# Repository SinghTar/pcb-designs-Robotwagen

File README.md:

# PCB designs

## Linetrackerboard versie 1

Hieronder vindt u de schema en de pcb design van de linetrackerbordje.

### schema 

### pcb

### 3D design

## Motorsturing versie 1

Hieronder vindt u de schema en de pcb design van de motorsturing.

### schema 

### pcb

### 3D design

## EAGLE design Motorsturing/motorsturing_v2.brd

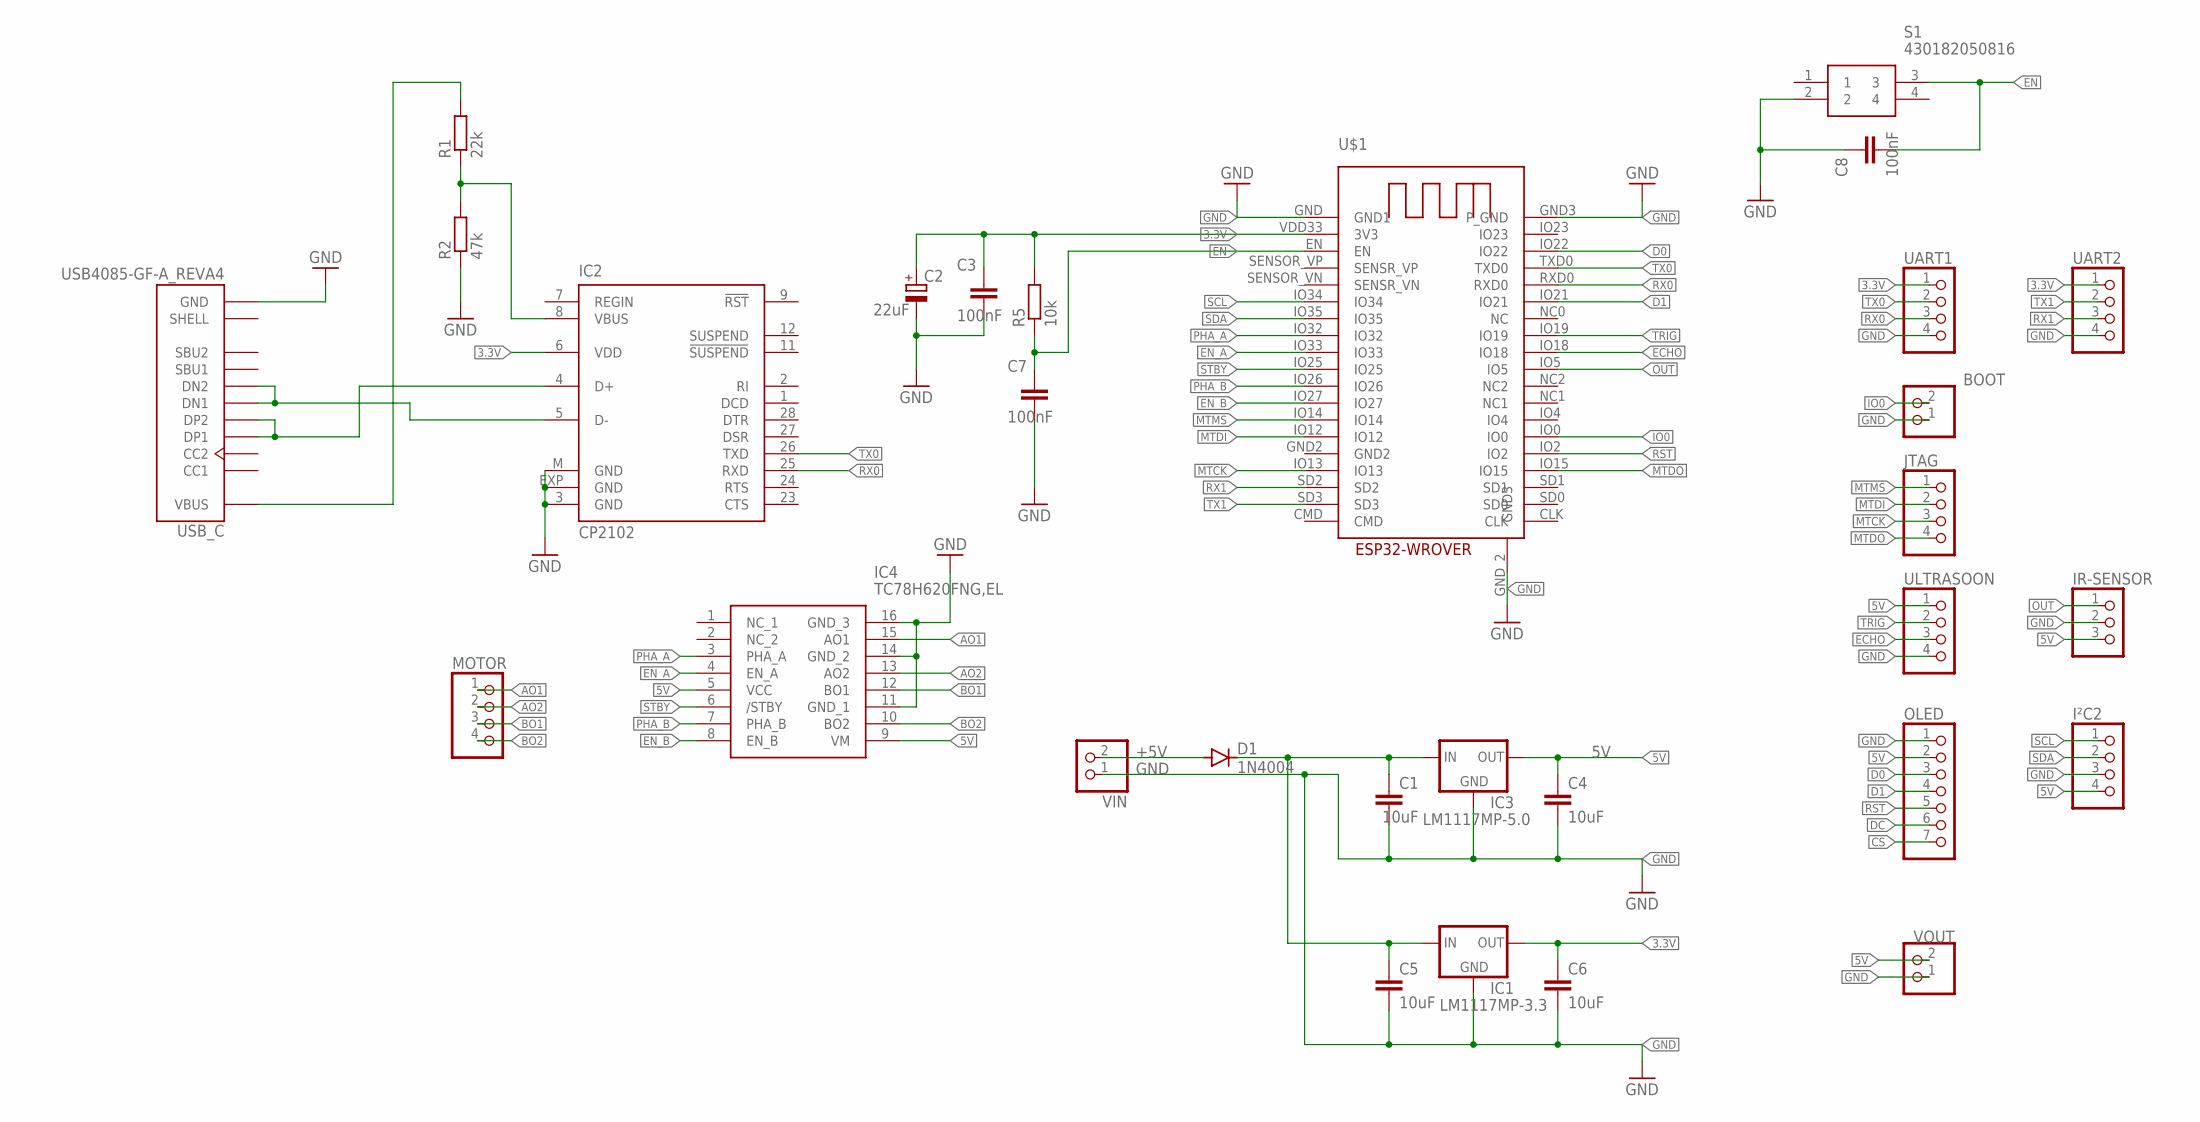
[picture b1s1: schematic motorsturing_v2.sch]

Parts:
BOOT: PINHD-1X2; 1X02
C1, C4, C5, C6: 10uF; C0603
C2: 22uF; E5-4
C3, C7, C8: 100nF; C0805
D1: 1N4004; DO41-10
IC1: LM1117MP-3.3; SOT223
IC2: CP2102; MLP28
IC3: LM1117MP-5.0; SOT223
IC4: TC78H620FNG,EL; SOP65P640X160-16N
IR-SENSOR: PINHD-1X3; 1X03
I²C2: PINHD-1X4; 1X04
JTAG: PINHD-1X4; 1X04
MOTOR: PINHD-1X4; 1X04
OLED: PINHD-1X7; 1X07
R1: 22k; M0805
R2: 47k; M0805
R5: 10k; M0805
S1: 430182050816; 430182070816
U$1: ESP32-WROVER
UART1, UART2: PINHD-1X4; 1X04
ULTRASOON: PINHD-1X4; 1X04
USB_C: USB4085-GF-A_REVA4; GCT_USB4085-GF-A_REVA4
VIN: PINHD-1X2; 1X02
VOUT: PINHD-1X2; 1X02

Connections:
3.3V: C2.+, C3.2, C6.1, IC1.2 (OUT), IC1.4 (OUT), IC2.6 (VDD), R5.2, U$1.VDD33 (3V3), UART1.1, UART2.1
5V: C4.1, IC3.2 (OUT), IC3.4 (OUT), IC4.5 (VCC), IC4.9 (VM), IR-SENSOR.3, I²C2.4, OLED.2, ULTRASOON.1, VOUT.2
+5V: C1.1, C5.1, D1.A, D1.C, IC1.3 (IN), IC3.3 (IN), VIN.2
AO1: IC4.15 (AO1), MOTOR.1
AO2: IC4.13 (AO2), MOTOR.2
BO1: IC4.12 (BO1), MOTOR.3
BO2: IC4.10 (BO2), MOTOR.4
CS: OLED.7
D0: OLED.3, U$1.IO22
D1: OLED.4, U$1.IO21
D+: IC2.4 (D+), USB_C.A6 (DP1), USB_C.B6 (DP2)
D-: IC2.5 (D-), USB_C.A7 (DN1), USB_C.B7 (DN2)
DC: OLED.6
ECHO: U$1.IO18, ULTRASOON.3
EN: C7.2, C8.1, R5.1, S1.3, U$1.EN
EN_A: IC4.4 (EN_A), U$1.IO33
EN_B: IC4.8 (EN_B), U$1.IO27
GND: BOOT.1, C1.2, C2.-, C3.1, C4.2, C5.2, C6.2, C7.1, C8.2, IC1.1 (GND), IC2.3 (GND), IC2.EXP (GND), IC2.M (GND), IC3.1 (GND), IC4.11 (GND_1), IC4.14 (GND_2), IC4.16 (GND_3), IR-SENSOR.2, I²C2.3, OLED.1, R2.1, S1.2, U$1.GND (GND1), U$1.GND3 (P_GND), U$1.GND_2 (GND3), UART1.4, UART2.4, ULTRASOON.4, USB_C.A1 (GND), USB_C.A12 (GND), USB_C.B1 (GND), USB_C.B12 (GND), VIN.1, VOUT.1
IO0: BOOT.2, U$1.IO0
MTCK: JTAG.3, U$1.IO13
MTDI: JTAG.2, U$1.IO12
MTDO: JTAG.4, U$1.IO15
MTMS: JTAG.1, U$1.IO14
OUT: IR-SENSOR.1, U$1.IO5
PHA_A: IC4.3 (PHA_A), U$1.IO32
PHA_B: IC4.7 (PHA_B), U$1.IO26
RST: OLED.5, U$1.IO2
RX0: IC2.25 (RXD), U$1.RXD0, UART1.3
RX1: U$1.SD2, UART2.3
SCL: I²C2.1, U$1.IO34
SDA: I²C2.2, U$1.IO35
STBY: IC4.6 (/STBY), U$1.IO25
TRIG: U$1.IO19, ULTRASOON.2
TX0: IC2.26 (TXD), U$1.TXD0, UART1.2
TX1: U$1.SD3, UART2.2
VBUS: IC2.8 (VBUS), R1.1, R1.2, R2.2, USB_C.A4 (VBUS), USB_C.A9 (VBUS), USB_C.B4 (VBUS), USB_C.B9 (VBUS)

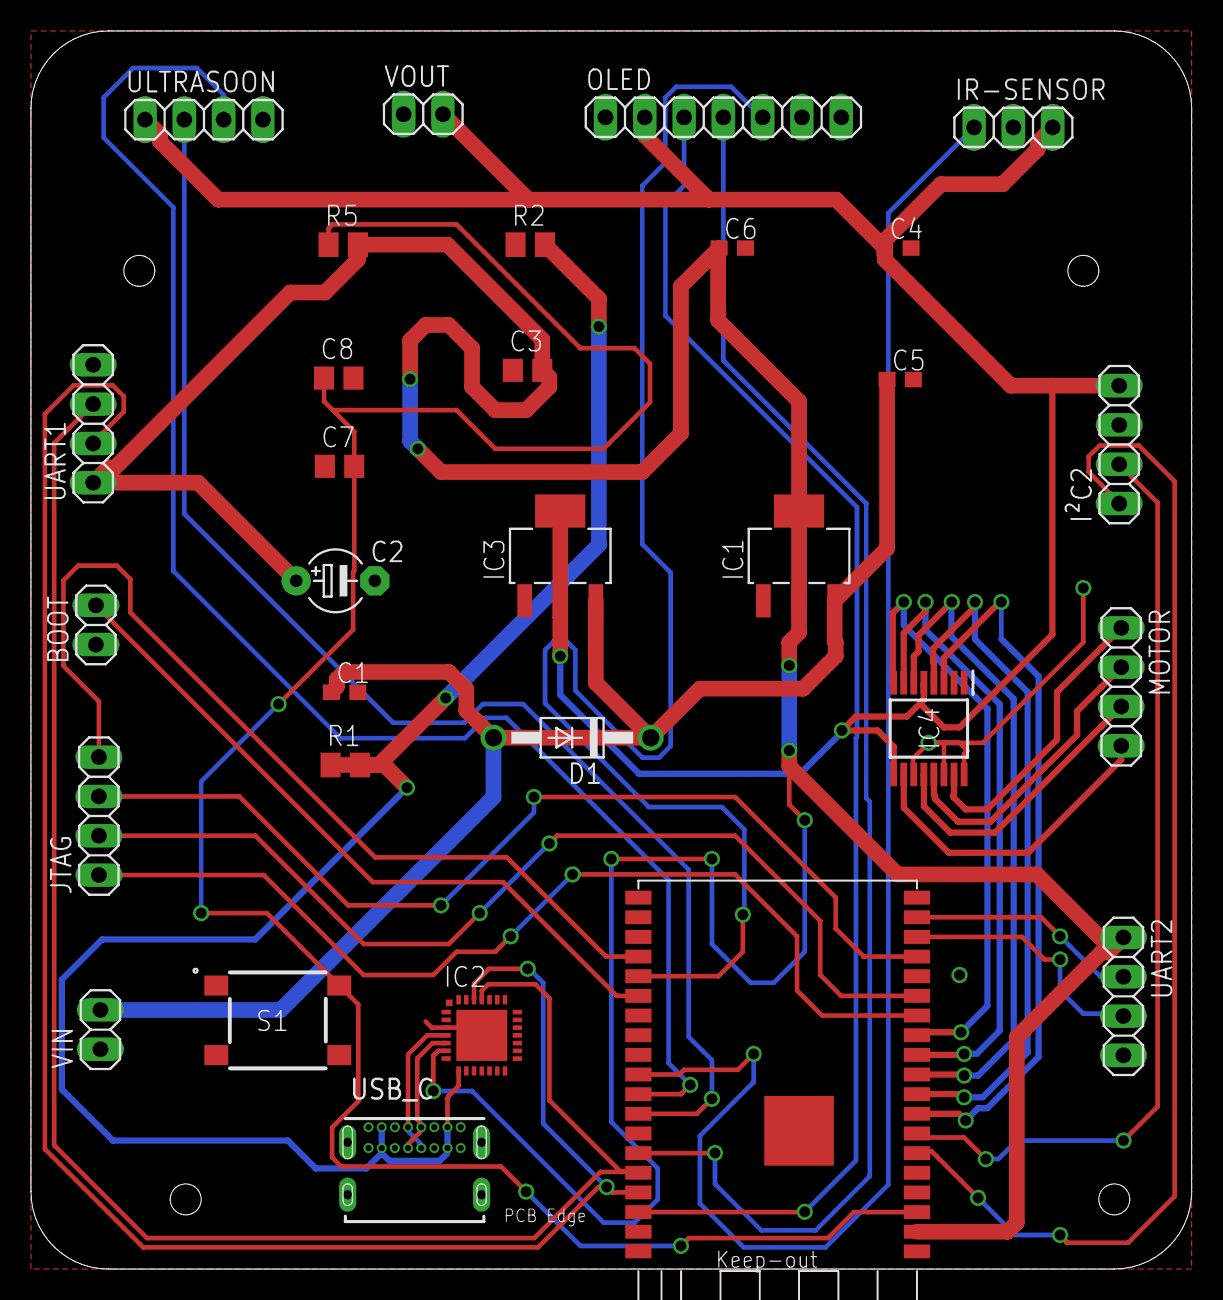
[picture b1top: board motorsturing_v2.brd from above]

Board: 2 copper layers, 75.0 x 80.0 mm, 30 parts (0 on the bottom side), 34 nets.

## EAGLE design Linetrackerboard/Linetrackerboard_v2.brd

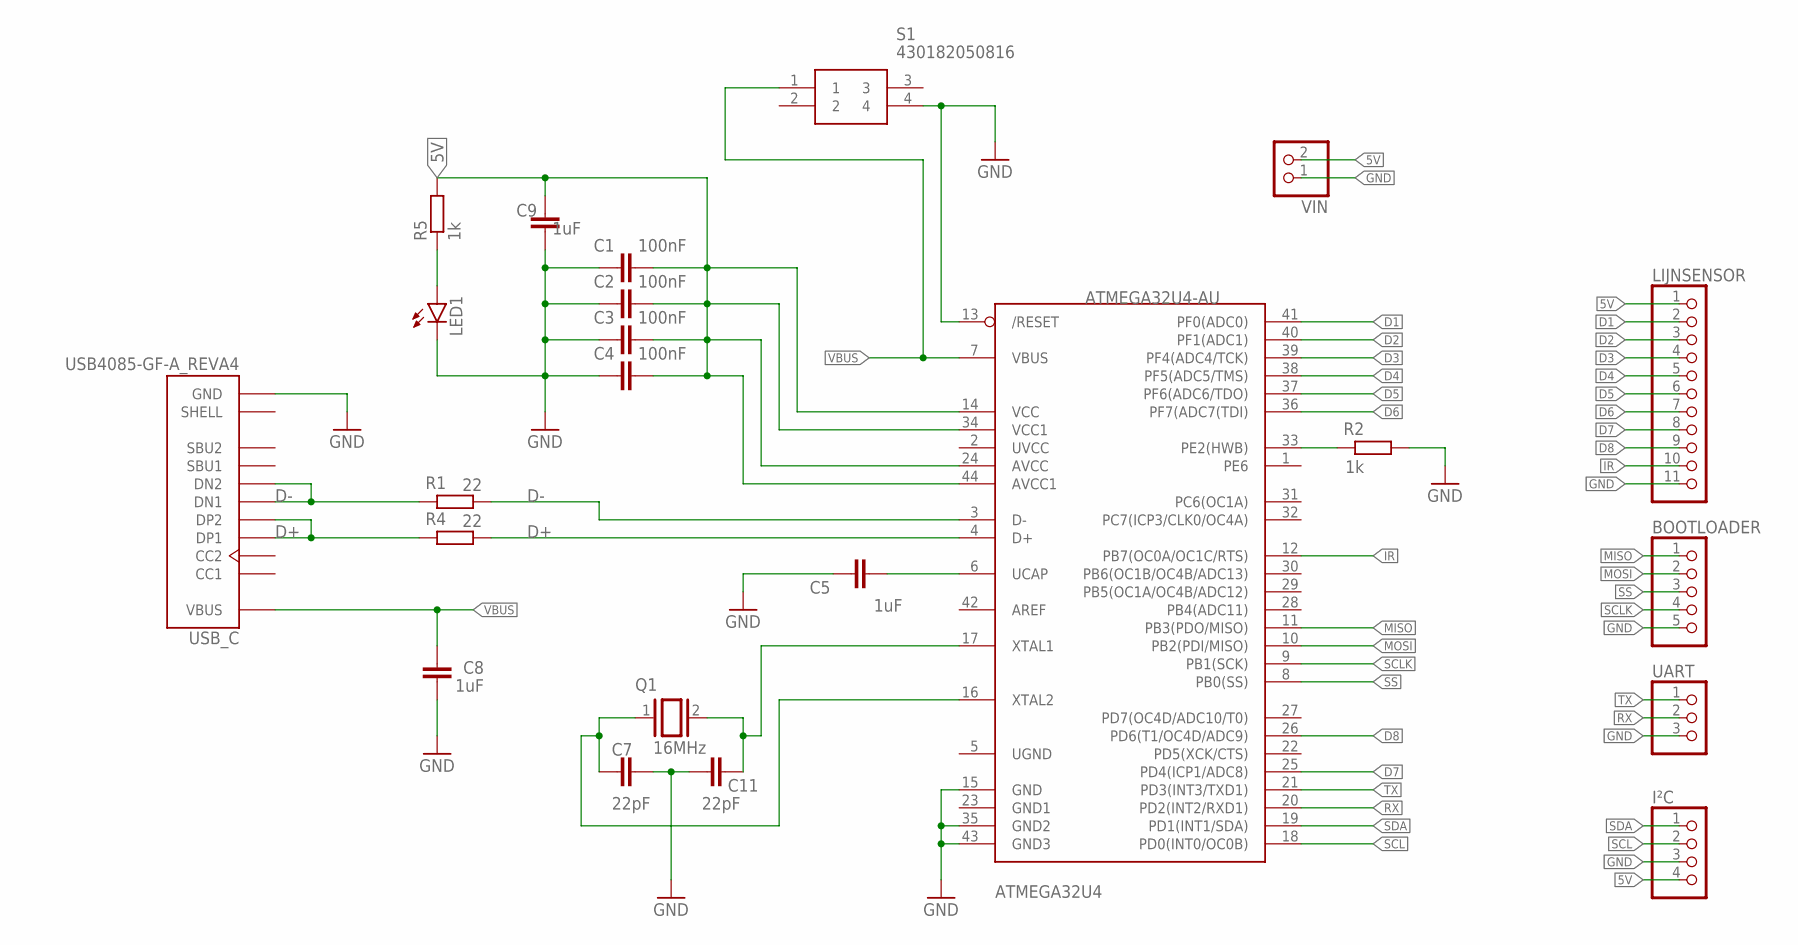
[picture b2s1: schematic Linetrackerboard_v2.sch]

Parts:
ATMEGA32U4: ATMEGA32U4-AU; TQFP44
BOOTLOADER: PINHD-1X5; 1X05
C1, C2, C3, C4: 100nF; C0805
C5: 1uF; C0805
C7, C11: 22pF; C0805
C8, C9: 1uF; C0603
I²C: PINHD-1X4; 1X04
LED1: LED; SMARTLED-TTW
LIJNSENSOR: PINHD-1X11; 1X11
Q1: 16MHz; QS
R1, R4: 22; M0805
R2, R5: 1k; M0805
S1: 430182050816; 430182070816
UART: PINHD-1X3; 1X03
USB_C: USB4085-GF-A_REVA4; GCT_USB4085-GF-A_REVA4
VIN: PINHD-1X2; 1X02

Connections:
5V: ATMEGA32U4.14 (VCC), ATMEGA32U4.24 (AVCC), ATMEGA32U4.34 (VCC1), ATMEGA32U4.44 (AVCC1), C1.2, C2.2, C3.2, C4.2, C9.2, I²C.4, LIJNSENSOR.1, R5.2, VIN.2
D1: ATMEGA32U4.41 (PF0(ADC0)), LIJNSENSOR.2
D2: ATMEGA32U4.40 (PF1(ADC1)), LIJNSENSOR.3
D3: ATMEGA32U4.39 (PF4(ADC4/TCK)), LIJNSENSOR.4
D4: ATMEGA32U4.38 (PF5(ADC5/TMS)), LIJNSENSOR.5
D5: ATMEGA32U4.37 (PF6(ADC6/TDO)), LIJNSENSOR.6
D6: ATMEGA32U4.36 (PF7(ADC7(TDI)), LIJNSENSOR.7
D7: ATMEGA32U4.25 (PD4(ICP1/ADC8)), LIJNSENSOR.8
D8: ATMEGA32U4.26 (PD6(T1/OC4D/ADC9)), LIJNSENSOR.9
D+: ATMEGA32U4.4 (D+), R4.1, R4.2, USB_C.A6 (DP1), USB_C.B6 (DP2)
D-: ATMEGA32U4.3 (D-), R1.1, R1.2, USB_C.A7 (DN1), USB_C.B7 (DN2)
GND: ATMEGA32U4.13 (/RESET), ATMEGA32U4.15 (GND), ATMEGA32U4.35 (GND2), ATMEGA32U4.43 (GND3), BOOTLOADER.5, C1.1, C2.1, C3.1, C4.1, C5.1, C7.2, C8.2, C9.1, C11.1, I²C.3, LED1.C@1 (C), LIJNSENSOR.11, R2.1, S1.4, UART.3, USB_C.A1 (GND), USB_C.A12 (GND), USB_C.B1 (GND), USB_C.B12 (GND), VIN.1
IR: ATMEGA32U4.12 (PB7(OC0A/OC1C/RTS)), LIJNSENSOR.10
MISO: ATMEGA32U4.11 (PB3(PDO/MISO)), BOOTLOADER.1
MOSI: ATMEGA32U4.10 (PB2(PDI/MISO)), BOOTLOADER.2
unnamed: LED1.A@1 (A), R5.1
PE2: ATMEGA32U4.33 (PE2(HWB)), R2.2
RX: ATMEGA32U4.20 (PD2(INT2/RXD1)), UART.2
SCL: ATMEGA32U4.18 (PD0(INT0/OC0B)), I²C.2
SCLK: ATMEGA32U4.9 (PB1(SCK)), BOOTLOADER.4
SDA: ATMEGA32U4.19 (PD1(INT1/SDA)), I²C.1
SS: ATMEGA32U4.8 (PB0(SS)), BOOTLOADER.3
TX: ATMEGA32U4.21 (PD3(INT3/TXD1)), UART.1
UCAP: ATMEGA32U4.6 (UCAP), C5.2
VBUS: ATMEGA32U4.7 (VBUS), C8.1, S1.1, USB_C.A4 (VBUS), USB_C.A9 (VBUS), USB_C.B4 (VBUS), USB_C.B9 (VBUS)
XTAL1: ATMEGA32U4.17 (XTAL1), C11.2, Q1.2
XTAL2: ATMEGA32U4.16 (XTAL2), C7.1, Q1.1

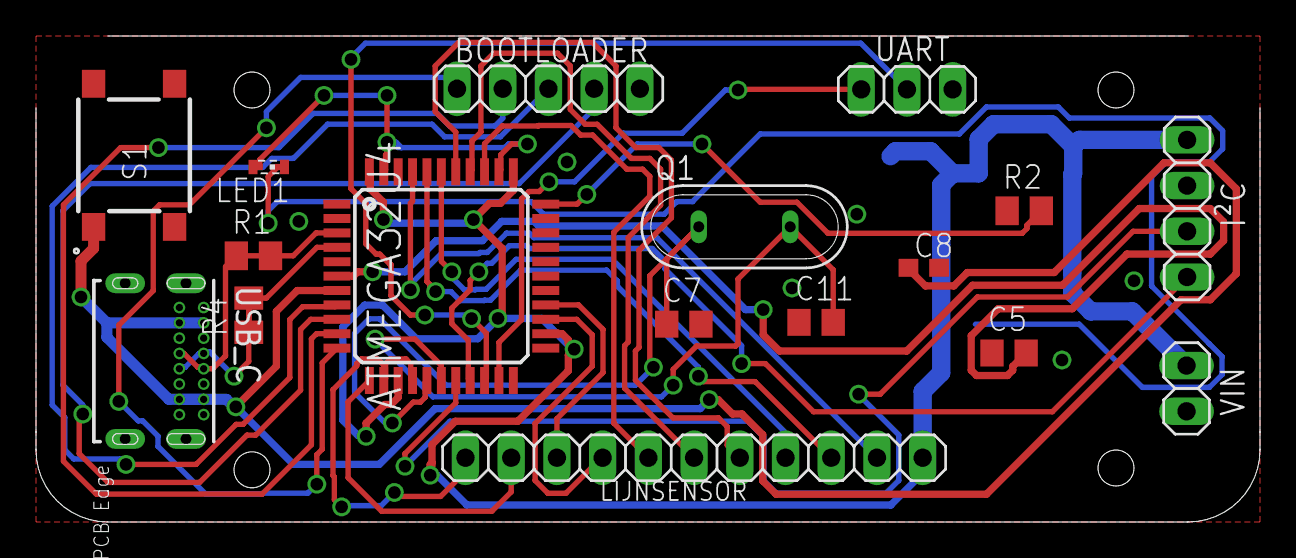
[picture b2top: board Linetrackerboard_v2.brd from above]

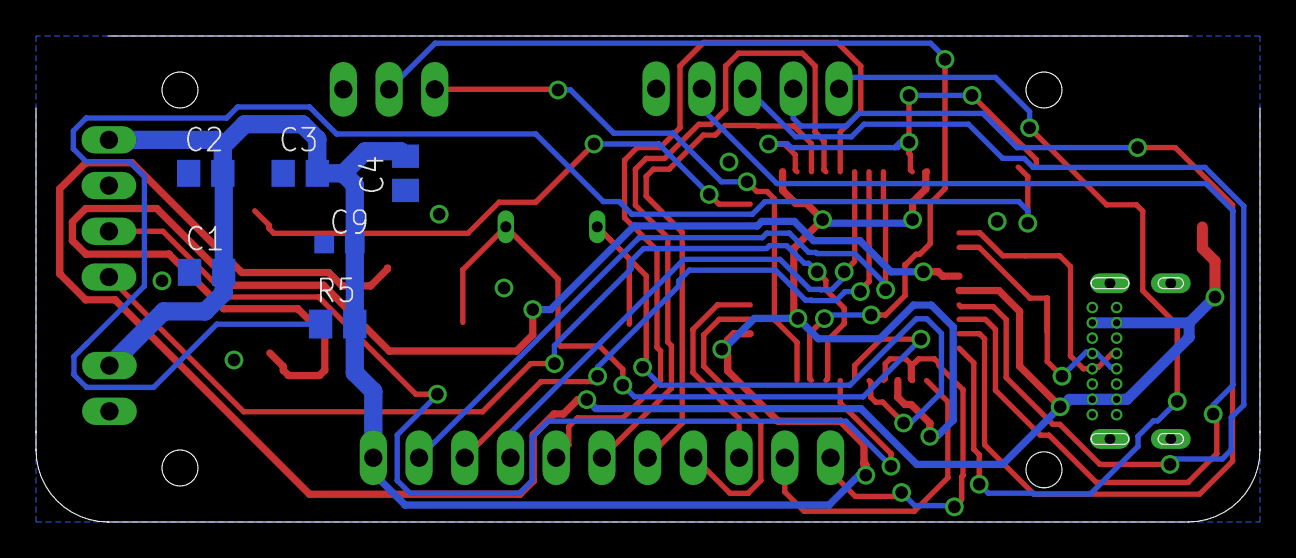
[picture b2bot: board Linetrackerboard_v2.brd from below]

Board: 2 copper layers, 68.0 x 27.0 mm, 23 parts (6 on the bottom side), 27 nets.

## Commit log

2022-04-30 new file: .nojekyll modified: README.md new file: assets/linetrackerboard/3D_linetrackerboard_achterkant.png new file: assets/linetrackerboard/3D_linetrackerboard_voorkant.png new file: assets/linetr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
2022-05-01 new file: Linetrackerboard/Linetrackerboard.brd new file: Linetrackerboard/Linetrackerboard.sch new file: Motorsturing/motorsturing.brd new file: Motorsturing/motorsturing.sch
2022-06-17 Rename pcb designs robotwagen.md to pcb designs robotwagen (documentatie).md
2022-06-17 Rename pcb designs robotwagen (documentatie).md to pcb designs documentatie.md
